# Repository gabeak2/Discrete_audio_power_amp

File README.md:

# Discrete_audio_power_amp
Discrete audio power amp to be driven from +/-15V, up to maybe +/-20V.  Sounds pretty nice!
https://youtube.com/shorts/sNpMInGTzjI?si=1pyV5VvMWjmVUsjt

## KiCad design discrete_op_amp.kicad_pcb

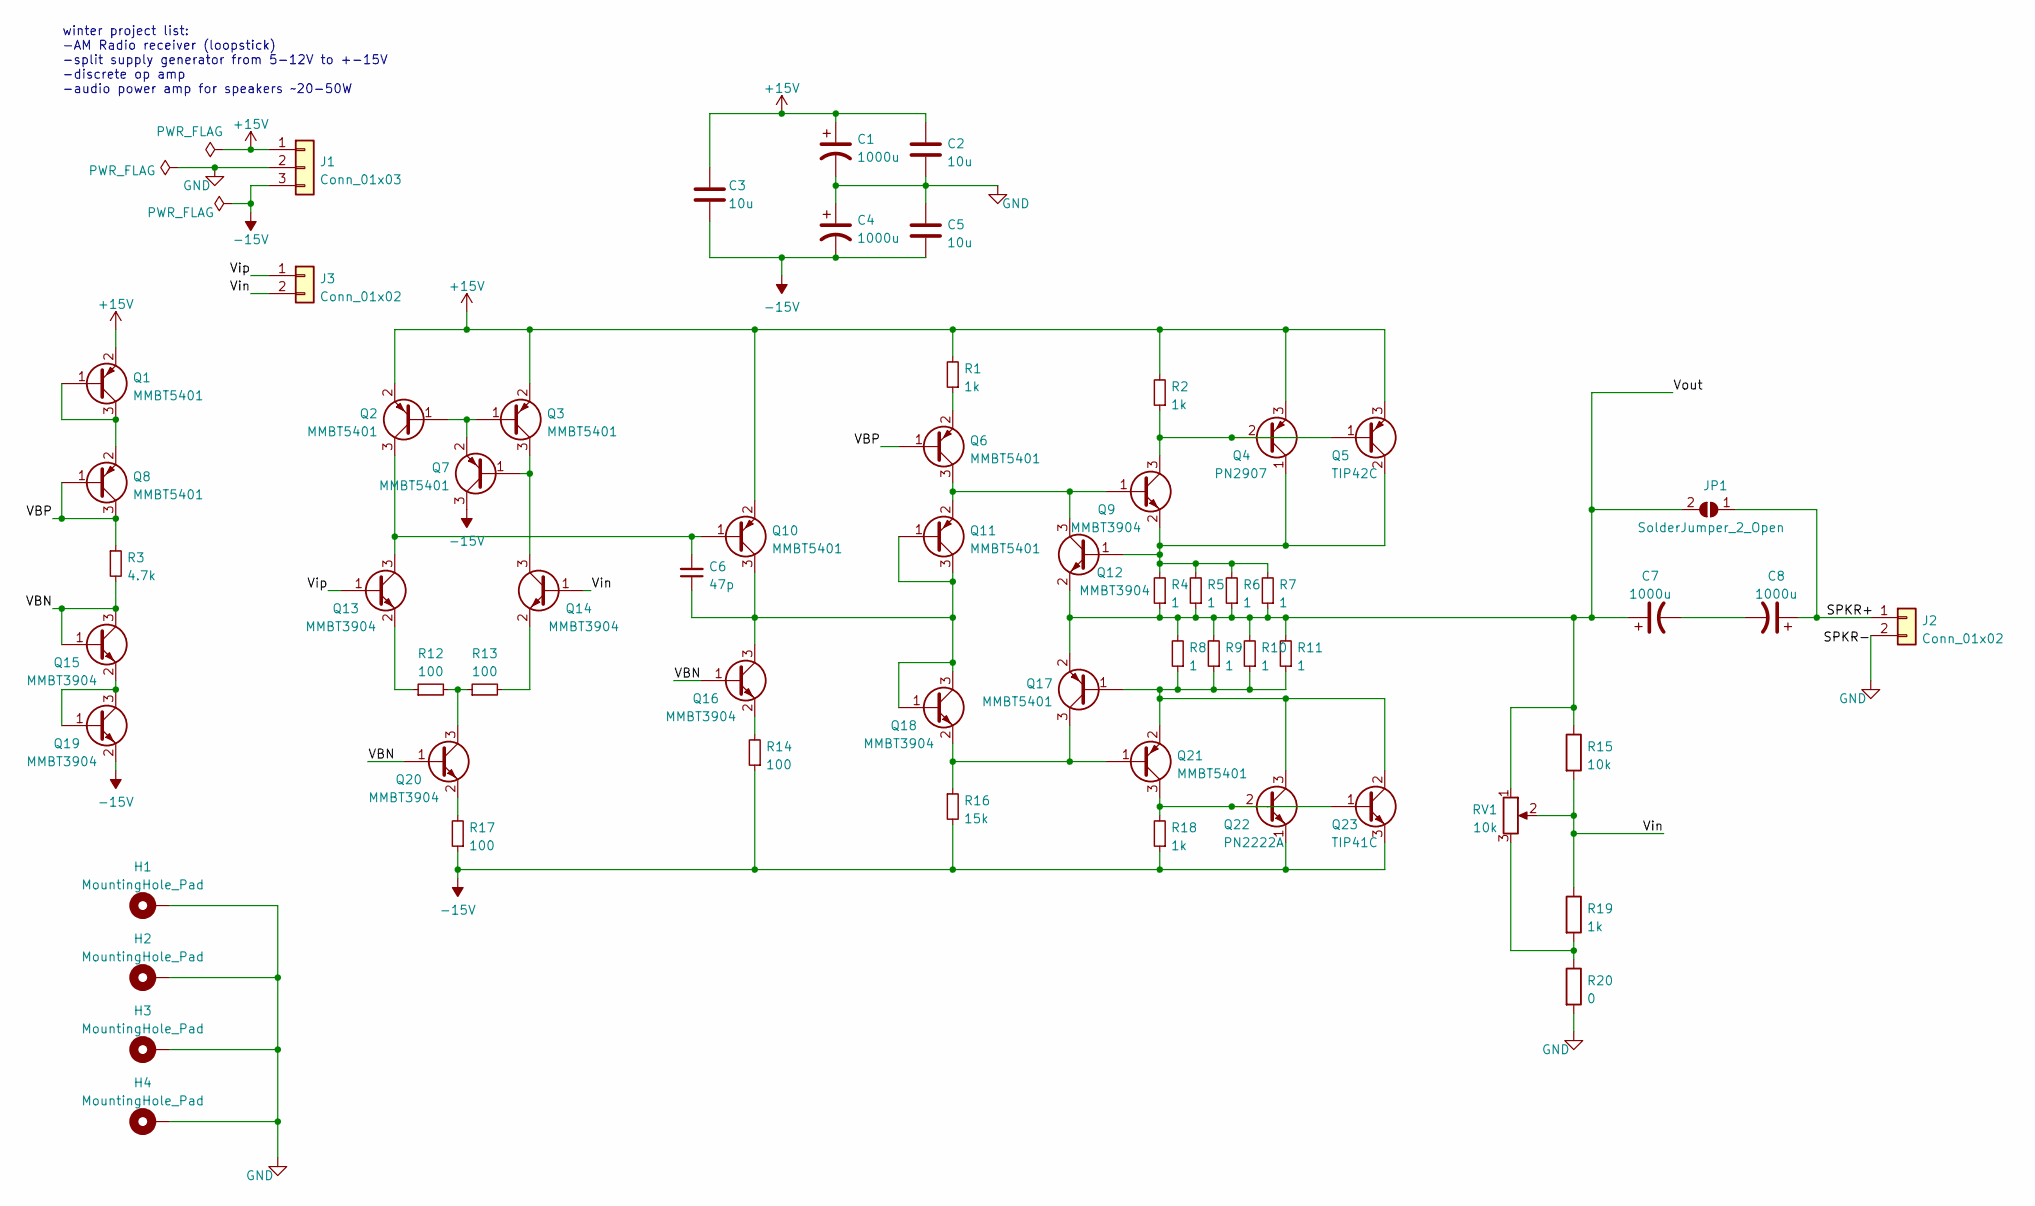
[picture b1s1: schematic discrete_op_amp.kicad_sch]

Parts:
C1, C4, C7, C8: 1000u; cap_elect_CS1E102M-CRI13; LCSC PN C123705
C2, C3, C5: 10u; C_0805_2012Metric; LCSC PN C440198
C6: 47p; C_0805_2012Metric; LCSC PN C49678
H1, H2, H3, H4: MountingHole_Pad; MountingHole_2.2mm_M2_DIN965_Pad
J1: Conn_01x03; TerminalBlock_bornier-3_P5.08mm
J2, J3: Conn_01x02; TerminalBlock_bornier-2_P5.08mm
JP1: SolderJumper_2_Open; SolderJumper-2_P1.3mm_Open_Pad1.0x1.5mm
Q1, Q2, Q3, Q6, Q7, Q8, Q10, Q11, Q17, Q21: MMBT5401; SOT-23; LCSC PN C8326
Q4: PN2907; TO-92_Inline
Q5: TIP42C; TO-220-3_Vertical
Q9, Q12, Q13, Q14, Q15, Q16, Q18, Q19, Q20: MMBT3904; SOT-23; LCSC PN C20526
Q22: PN2222A; TO-92_Inline
Q23: TIP41C; TO-220-3_Vertical
R1, R2, R18: 1k; R_0805_2012Metric; LCSC PN C17513
R3: 4.7k; R_0805_2012Metric; LCSC PN C17475
R4, R5, R6, R7, R8, R9, R10, R11: 1; R_0805_2012Metric; LCSC PN C25271
R12, R13, R14, R17: 100; R_0805_2012Metric; LCSC PN C17513
R15: 10k; R_0805_2012Metric; LCSC PN C17414
R16: 15k; R_0805_2012Metric; LCSC PN C17475
R19: 1k; R_0805_2012Metric; LCSC C17513
R20: 0; R_0805_2012Metric; LCSC C17477
RV1: 10k; bourns_10k_pot_3306W

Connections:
+15V: C1.1, C2.1, C3.1, J1.1, Q1.2 (E), Q2.2 (E), Q3.2 (E), Q4.3 (E), Q5.3 (E), Q10.2 (E), R1.2, R2.2
-15V: C3.2, C4.2, C5.2, J1.3, Q7.3 (C), Q19.2 (E), Q22.1 (E), Q23.3 (E), R14.1, R16.2, R17.1, R18.1
/SPKR+: C8.1, J2.1, JP1.1 (A)
/VBN: Q15.1 (B), Q15.3 (C), Q16.1 (B), Q20.1 (B), R3.2
/VBP: Q6.1 (B), Q8.1 (B), Q8.3 (C), R3.1
/Vin: J3.2, Q14.1 (B), R15.2, R19.1, RV1.2
/Vip: J3.1, Q13.1 (B)
/Vout: C7.1, JP1.2 (B), Q12.2 (E), Q17.2 (E), R4.1, R5.1, R6.1, R7.1, R8.2, R9.2, R10.2, R11.2, R15.1, RV1.1
GND: C1.2, C2.2, C4.1, C5.1, H1.1, H2.1, H3.1, H4.1, J1.2, J2.2, R20.2
unnamed: C6.1, Q10.3 (C), Q11.1 (B), Q11.3 (C), Q16.3 (C), Q18.1 (B), Q18.3 (C)
unnamed: C6.2, Q2.3 (C), Q10.1 (B), Q13.3 (C)
unnamed: C7.2, C8.2
unnamed: Q1.1 (B), Q1.3 (C), Q8.2 (E)
unnamed: Q2.1 (B), Q3.1 (B), Q7.2 (E)
unnamed: Q4.2 (B), Q5.1 (B), Q9.3 (C), R2.1
unnamed: Q6.2 (E), R1.1
unnamed: Q6.3 (C), Q9.1 (B), Q11.2 (E), Q12.3 (C)
unnamed: Q4.1 (C), Q5.2 (C), Q9.2 (E), Q12.1 (B), R4.2, R5.2, R6.2, R7.2
unnamed: Q13.2 (E), R12.1
unnamed: Q14.2 (E), R13.2
unnamed: Q3.3 (C), Q7.1 (B), Q14.3 (C)
unnamed: Q15.2 (E), Q19.1 (B), Q19.3 (C)
unnamed: Q16.2 (E), R14.2
unnamed: Q17.1 (B), Q21.2 (E), Q22.3 (C), Q23.2 (C), R8.1, R9.1, R10.1, R11.1
unnamed: Q17.3 (C), Q18.2 (E), Q21.1 (B), R16.1
unnamed: Q20.2 (E), R17.2
unnamed: Q20.3 (C), R12.2, R13.1
unnamed: Q21.3 (C), Q22.2 (B), Q23.1 (B), R18.2
unnamed: R19.2, R20.1, RV1.3

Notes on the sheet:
winter project list: -AM Radio receiver (loopstick) -split supply generator from 5-12V to +-15V -discrete op amp -audio power amp for speakers ~20-50W

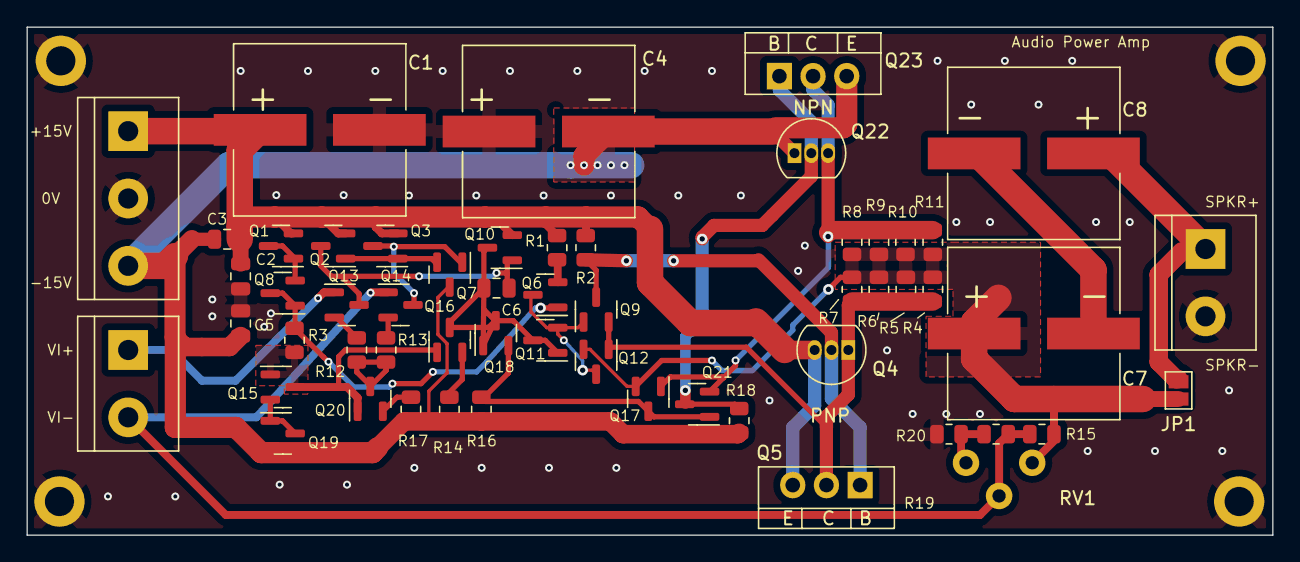
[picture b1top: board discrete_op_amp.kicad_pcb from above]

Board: 2 copper layers, 94.0 x 38.3 mm, 60 parts (0 on the bottom side), 29 nets.

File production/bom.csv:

Designator,Footprint,Quantity,Value,LCSC Part #
"C1, C4, C7, C8",cap_elect_CS1E102M-CRI13,4,1000u,
"C2, C3, C5",C_0805_2012Metric,3,10u,
C6,C_0805_2012Metric,1,47p,
"H1, H2, H3, H4",MountingHole_2.2mm_M2_DIN965_Pad,4,MountingHole_Pad,
J1,TerminalBlock_bornier-3_P5.08mm,1,Conn_01x03,
"J2, J3",TerminalBlock_bornier-2_P5.08mm,2,Conn_01x02,
JP1,SolderJumper-2_P1.3mm_Open_Pad1.0x1.5mm,1,SolderJumper_2_Open,
"Q1, Q10, Q11, Q17, Q2, Q21, Q3, Q6, Q7, Q8",SOT-23,10,MMBT5401,
"Q12, Q13, Q14, Q15, Q16, Q18, Q19, Q20, Q9",SOT-323_SC-70,9,FMMT491,
Q22,TO-92_Inline,1,PN2222A,
Q23,TO-220-3_Vertical,1,TIP41C,
Q4,TO-92_Inline,1,PN2907,
Q5,TO-220-3_Vertical,1,TIP42C,
"R1, R18, R19, R2",R_0805_2012Metric,4,1k,
"R10, R11, R4, R5, R6, R7, R8, R9",R_0805_2012Metric,8,1,
"R12, R13, R14, R17",R_0805_2012Metric,4,100,
R15,R_0805_2012Metric,1,10k,
R16,R_0805_2012Metric,1,15k,
R20,R_0805_2012Metric,1,0,C17477
R3,R_0805_2012Metric,1,4.7k,
